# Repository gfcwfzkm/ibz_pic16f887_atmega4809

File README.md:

# ibz_pic16f887_atmega4809
A basic adapter-board I've made to replace the slow PIC16F887 with a ATmega4809 on the dev board of the school. Might not be 100% compatible with the PIC's I/Os, but compatible enough to replace it on the dev board.

The BOM is so small that I didn't even made one, as the components used there are rather obvious.
The only special component used in the actual thing were the "Flip-Pins" from EvilMadScientist, since I did not want to stress / bend socket on the dev-board too much.

Image:

( Was testing / working on a basic PID electro-heater project there )

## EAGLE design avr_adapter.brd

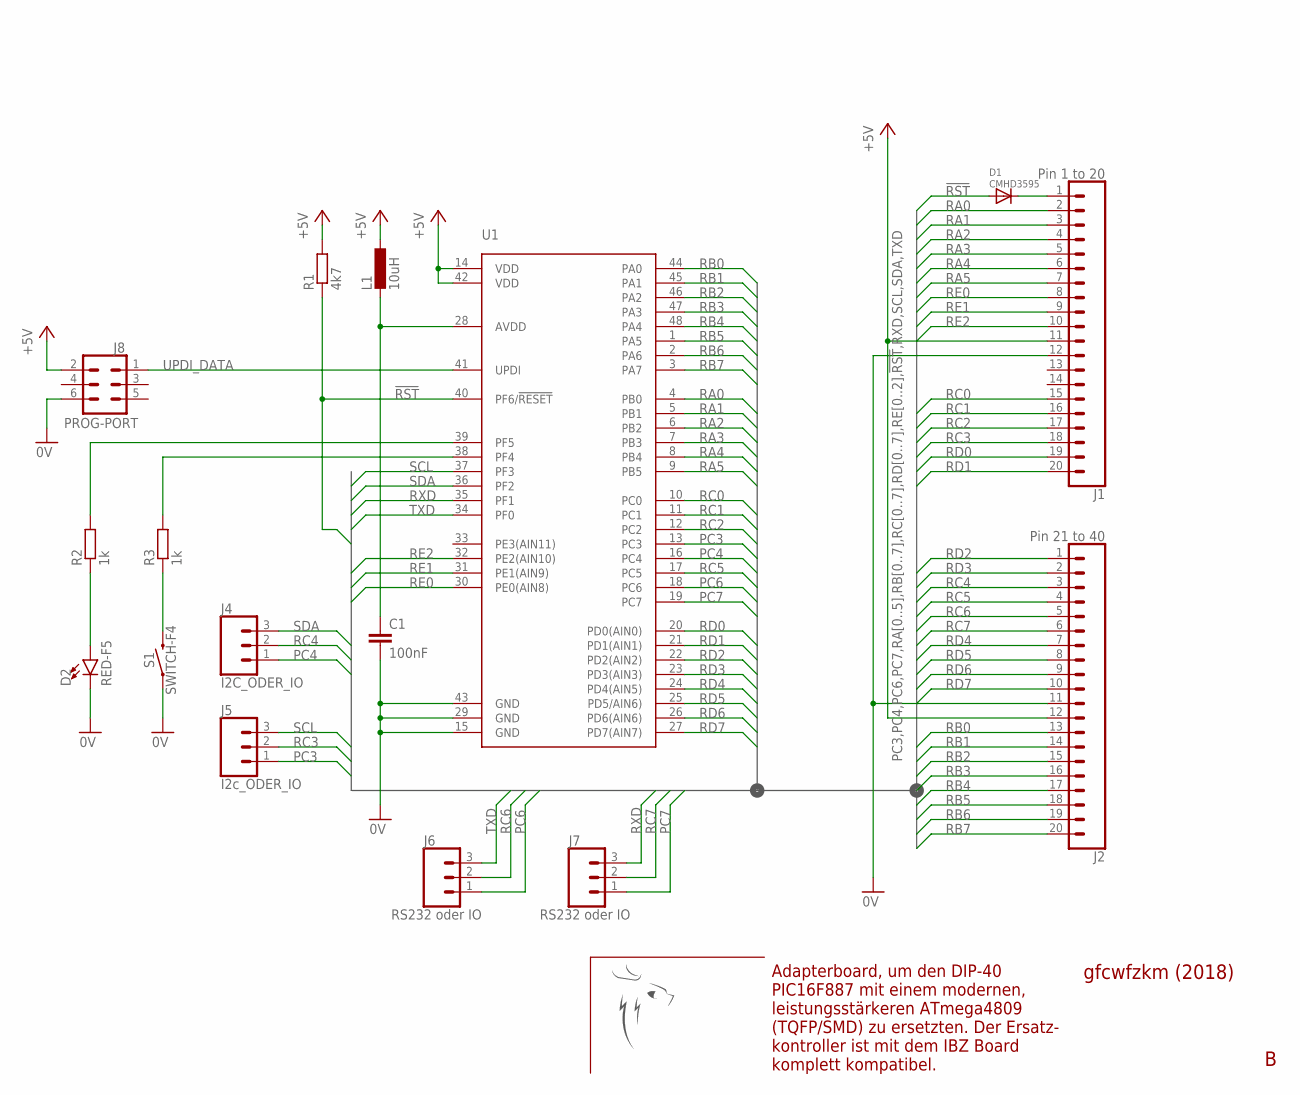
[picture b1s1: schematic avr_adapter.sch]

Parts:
C1: 100nF; C0805
D1: CMHD3595; SOD-123
D2: RED-F5; FKIT-LED-1206
J1: Pin 1 to 20; 1X20
J2: Pin 21 to 40; 1X20
J4: I2C_ODER_IO; 1X03
J5: I2c_ODER_IO; 1X03
J6, J7: RS232 oder IO; 1X03
J8: PROG-PORT; 2X3
L1: 10uH; L2012C
R1: 4k7; R0805
R2, R3: 1k; R0805
S1: SWITCH-F4; TACTILE_SWITCH_SMD_6.0X3.5MM
U1: ATMEGA4809ATMEGA4809_TQFP48; TQFP-48
U$1: LOGO_PASCAL_GESELLEMPTY; EMPTY

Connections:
0V: C1.2, D2.C, J1.12, J2.11, J8.6, S1.1, U1.15 (GND), U1.29 (GND), U1.43 (GND)
!RST: D1.A, R1.1, U1.40 (PF6/!RESET)
+5V: J1.11, J2.12, J8.2, L1.1, R1.2, U1.14 (VDD), U1.42 (VDD)
unnamed: D1.C, J1.1
unnamed: R2.2, U1.39 (PF5)
unnamed: C1.1, L1.2, U1.28 (AVDD)
unnamed: R3.2, U1.38 (PF4)
unnamed: D2.A, R2.1
unnamed: R3.1, S1.2
PC3: J5.1, U1.13 (PC3)
PC4: J4.1, U1.16 (PC4)
PC6: J6.1, U1.18 (PC6)
PC7: J7.1, U1.19 (PC7)
RA0: J1.2, U1.4 (PB0)
RA1: J1.3, U1.5 (PB1)
RA2: J1.4, U1.6 (PB2)
RA3: J1.5, U1.7 (PB3)
RA4: J1.6, U1.8 (PB4)
RA5: J1.7, U1.9 (PB5)
RB0: J2.13, U1.44 (PA0)
RB1: J2.14, U1.45 (PA1)
RB2: J2.15, U1.46 (PA2)
RB3: J2.16, U1.47 (PA3)
RB4: J2.17, U1.48 (PA4)
RB5: J2.18, U1.1 (PA5)
RB6: J2.19, U1.2 (PA6)
RB7: J2.20, U1.3 (PA7)
RC0: J1.15, U1.10 (PC0)
RC1: J1.16, U1.11 (PC1)
RC2: J1.17, U1.12 (PC2)
RC3: J1.18, J5.2
RC4: J2.3, J4.2
RC5: J2.4, U1.17 (PC5)
RC6: J2.5, J6.2
RC7: J2.6, J7.2
RD0: J1.19, U1.20 (PD0(AIN0))
RD1: J1.20, U1.21 (PD1(AIN1))
RD2: J2.1, U1.22 (PD2(AIN2))
RD3: J2.2, U1.23 (PD3(AIN3))
RD4: J2.7, U1.24 (PD4(AIN5))
RD5: J2.8, U1.25 (PD5/AIN6))
RD6: J2.9, U1.26 (PD6(AIN6))
RD7: J2.10, U1.27 (PD7(AIN7))
RE0: J1.8, U1.30 (PE0(AIN8))
RE1: J1.9, U1.31 (PE1(AIN9))
RE2: J1.10, U1.32 (PE2(AIN10))
RXD: J7.3, U1.35 (PF1)
SCL: J5.3, U1.37 (PF3)
SDA: J4.3, U1.36 (PF2)
TXD: J6.3, U1.34 (PF0)
UPDI_DATA: J8.1, U1.41 (UPDI)

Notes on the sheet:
gfcwfzkm (2018)
Adapterboard, um den DIP-40 PIC16F887 mit einem modernen, leistungsstärkeren ATmega4809 (TQFP/SMD) zu ersetzten. Der Ersatz- kontroller ist mit dem IBZ Board komplett kompatibel.

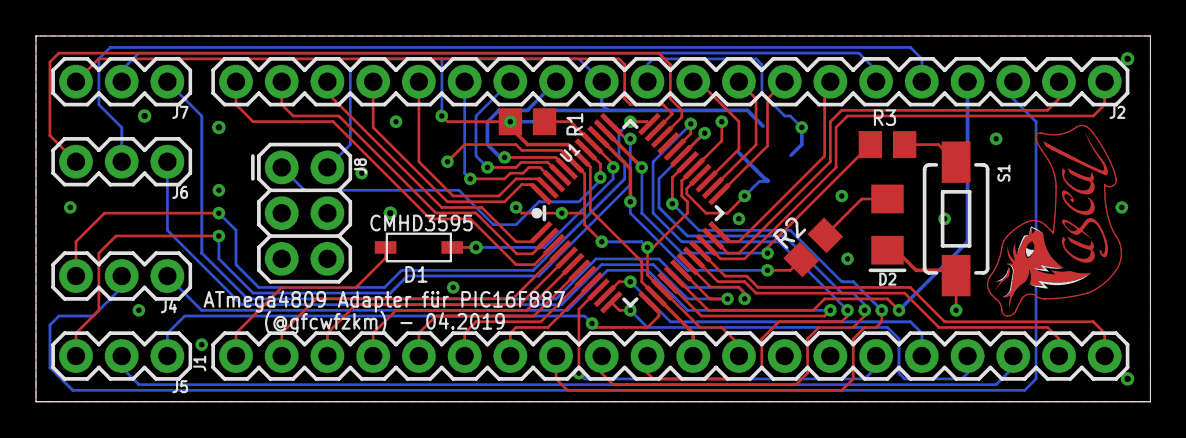
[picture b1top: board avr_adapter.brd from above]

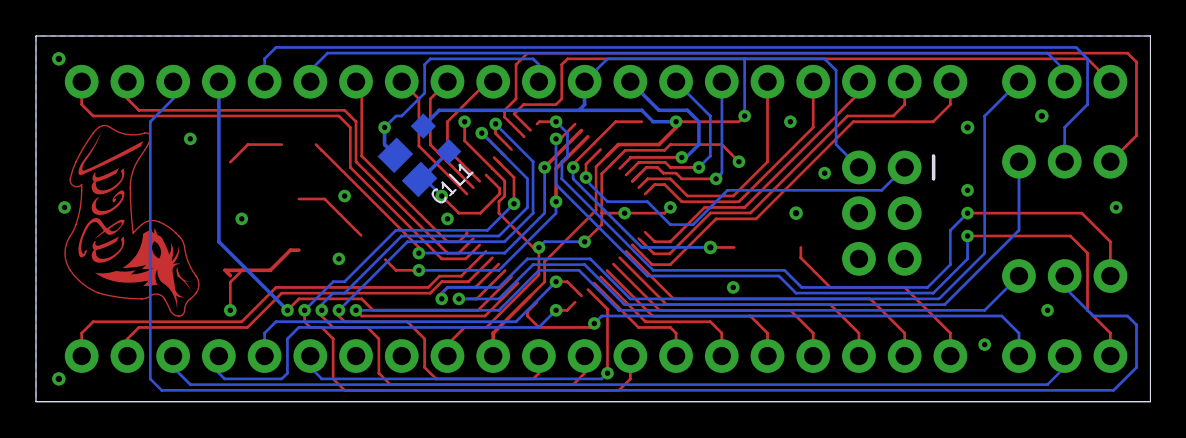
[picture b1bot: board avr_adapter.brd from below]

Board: 2 copper layers, 61.9 x 20.3 mm, 17 parts (2 on the bottom side), 51 nets.

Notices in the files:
parts and their libraries:
SparkFun-Connectors: Licensing: Creative Commons ShareAlike 4.0 International - https://creativecommons.org/licenses/by-sa/4.0
